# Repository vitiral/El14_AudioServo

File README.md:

Design Taken from http://www.scary-terry.com/audioservo/audioservo.htm

Used to demonstrate beta version of Cadsoft Eagle v7

7/6 SCK edited to add 555 timer

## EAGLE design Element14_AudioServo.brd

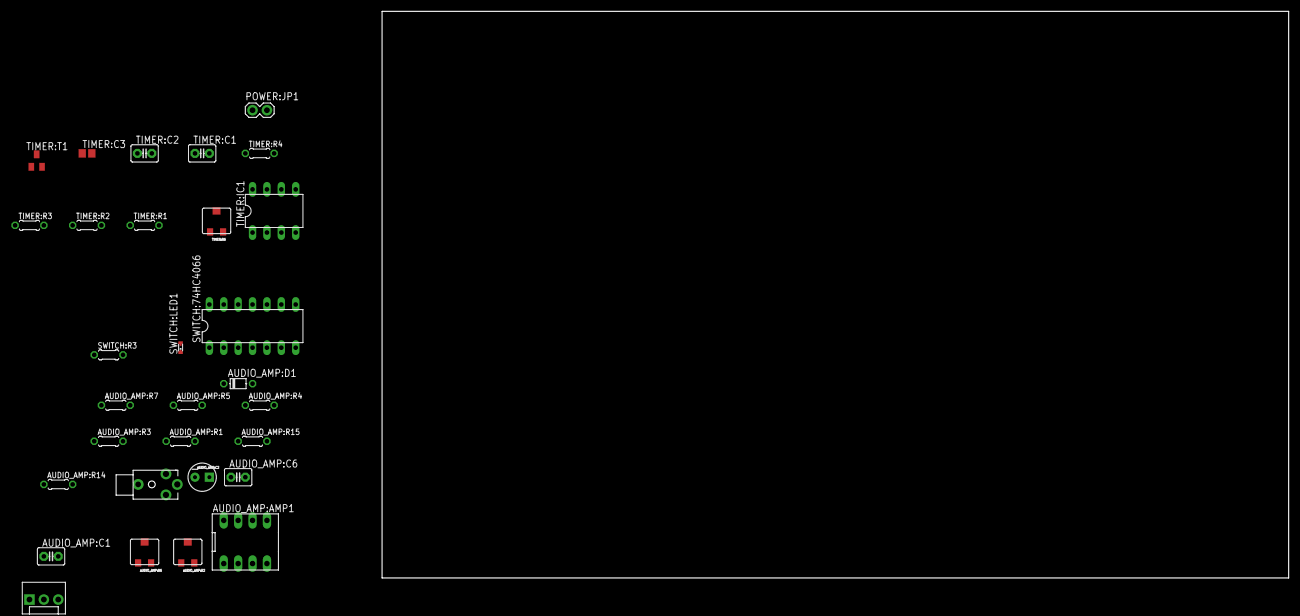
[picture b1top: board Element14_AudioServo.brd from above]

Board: 2 copper layers, 160.0 x 100.0 mm, 30 parts (0 on the bottom side), 24 nets, no tracks yet.

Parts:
AUDIO_AMP:AMP1: MC1458; DIP8
AUDIO_AMP:C1, AUDIO_AMP:C6: 0.1uF; C2.5-3
AUDIO_AMP:C2: 10uF; CPOL-RADIAL-10UF-25V
AUDIO_AMP:D1: D-5
AUDIO_AMP:JP1: STEREOJACK2.5MM_STEREOJACK2.5MM
AUDIO_AMP:R1: 1k; 0204/5
AUDIO_AMP:R2, AUDIO_AMP:R6: 1k; PVG3
AUDIO_AMP:R3, AUDIO_AMP:R4: 47k; 0204/5
AUDIO_AMP:R5, AUDIO_AMP:R7, AUDIO_AMP:R15: 10k; 0204/5
AUDIO_AMP:R14: 2.2k; 0204/5
POWER:JP1: M02PTH; 1X02
SWITCH:74HC4066: U1; DIP14
SWITCH:LED1: SMARTLED-TTW
SWITCH:R3: 0204/5
TIMER:C1: 0.01uF; C2.5-3
TIMER:C2: 0.1uF; C2.5-3
TIMER:C3: 470uF; C0805
TIMER:IC1: NE555; DIL-08
TIMER:JP1: MOLEX-1X3
TIMER:R1: 220k; 0204/5
TIMER:R2: 4.7k; 0204/5
TIMER:R3, TIMER:R4: 10k; 0204/5
TIMER:R6: 50k; PVG3
TIMER:T1: SOT23-EBC

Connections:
+5V: POWER:JP1.2, SWITCH:74HC4066.14, SWITCH:R3.2, TIMER:C3.1, TIMER:IC1.4, TIMER:IC1.8, TIMER:JP1.2, TIMER:R1.2, TIMER:R4.1
AUDIO_AMP:AUDIO_IN: AUDIO_AMP:C1.1, AUDIO_AMP:JP1.TIP
AUDIO_AMP:N$1: AUDIO_AMP:AMP1.2, AUDIO_AMP:R1.2, AUDIO_AMP:R2.P$1
AUDIO_AMP:N$2: AUDIO_AMP:C1.2, AUDIO_AMP:R1.1
AUDIO_AMP:N$4: AUDIO_AMP:AMP1.7, AUDIO_AMP:D1.A
AUDIO_AMP:N$5: AUDIO_AMP:AMP1.3, AUDIO_AMP:R3.1, AUDIO_AMP:R4.2
AUDIO_AMP:N$6: AUDIO_AMP:R6.P$2, AUDIO_AMP:R7.2
AUDIO_AMP:N$7: AUDIO_AMP:AMP1.1, AUDIO_AMP:AMP1.6, AUDIO_AMP:R2.P$2, AUDIO_AMP:R2.P$3
AUDIO_AMP:N$8: AUDIO_AMP:C2.1, AUDIO_AMP:D1.C, AUDIO_AMP:R14.2
AUDIO_AMP:N$9: AUDIO_AMP:R5.1, AUDIO_AMP:R6.P$1
AUDIO_AMP:R6: AUDIO_AMP:AMP1.5, AUDIO_AMP:R6.P$3
GND: AUDIO_AMP:AMP1.4, AUDIO_AMP:C2.2, AUDIO_AMP:C6.1, AUDIO_AMP:JP1.RING1, AUDIO_AMP:R4.1, AUDIO_AMP:R7.1, AUDIO_AMP:R15.2, POWER:JP1.1, SWITCH:74HC4066.2, SWITCH:74HC4066.5, SWITCH:74HC4066.6, SWITCH:74HC4066.7, TIMER:C1.2, TIMER:C2.2, TIMER:C3.2, TIMER:IC1.1, TIMER:JP1.3, TIMER:T1.E
unnamed: AUDIO_AMP:AMP1.8, AUDIO_AMP:C6.2, AUDIO_AMP:R3.2, AUDIO_AMP:R5.2
unnamed: SWITCH:74HC4066.10, TIMER:R6.P$3
unnamed: AUDIO_AMP:R14.1, AUDIO_AMP:R15.1, SWITCH:74HC4066.12, SWITCH:74HC4066.13
unnamed: SWITCH:74HC4066.11, TIMER:R2.2, TIMER:R6.P$1
SWITCH:N$3: SWITCH:74HC4066.1, SWITCH:LED1.C@1
SWITCH:N$4: SWITCH:LED1.A@1, SWITCH:R3.1
TIMER:N$1: TIMER:C1.1, TIMER:IC1.5
TIMER:N$3: TIMER:IC1.3, TIMER:R3.2
TIMER:N$4: TIMER:R3.1, TIMER:T1.B
TIMER:N$7: TIMER:C2.1, TIMER:IC1.2, TIMER:IC1.6, TIMER:R2.1
TIMER:N$9: TIMER:IC1.7, TIMER:R1.1, TIMER:R6.P$2
TIMER:SERVO_OUT: TIMER:JP1.1, TIMER:R4.2, TIMER:T1.C

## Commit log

2014-07-04 first commit, blank files
2014-07-04 put some parts in
2014-07-06 Update Element14_AudioServo.brd
    Nothing seems to be visible in the board, added "//" to the end of the file so that Github would let me commit changes
2014-07-07 Made changes to schematic
2014-07-07 Update El14_AudioServo.lbr
    Added HC4066, potentiometer
2014-07-07 Update Element14_AudioServo.sch
    Added HC4066 block
2014-07-07 got board to populate
2014-07-07 added library
2014-07-07 random commit
2014-07-08 schematic ready for review

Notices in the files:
parts and their libraries:
SparkFun-Capacitors: Licensing: Creative Commons ShareAlike 4.0 International - https://creativecommons.org/licenses/by-sa/4.0
